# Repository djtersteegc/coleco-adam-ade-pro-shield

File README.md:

# coleco-adam-ade-pro-shield

This custom Arduino Mega 2560 shield compatible with [AdamNet Drive Emulator](https://github.com/Kalidomra/AdamNet-Drive-Emulator) (ADE) software by Sean Myers. The design is built to be compatible with the "Pro" version of the software available precompiled and ready for flashing on his repo.  I was inspired by John Lundy's original ADE shield design, but wanted something with a slightly smaller footprint and different SD card module.  This was accomplished by putting the LCD on stand-offs and mounting the card (and some other components) underneath it.

All components can be sourced from the usual low cost China based vendors for a total build cost of around $20.  Please see the assembly page for more details.

[Hardware Component Choices and Assembly](https://djtersteegc.github.io/coleco-adam-ade-pro-shield/assembly.html)

An interactive BOM and parts placement diagram is also available.

[Interactive Bill of Materials (BOM)](https://djtersteegc.github.io/coleco-adam-ade-pro-shield/ibom.html)

STL's and the [DesignSpark Mechanical](https://www.rs-online.com/designspark/mechanical-software) source file for a 3D printable enclosure are in the **enclosure** directory. There is a difference in power and USB connectors locations between the offical 2560 boards and the Chinese copies you can buy with the CH340 serial chips.  Pick the body file that matches the type you are using. The lid is snap fit, but you can also add a single M3x10mm screw if you wish to secure it further. Make sure to print seven copies of the button file.

If you wish to power your board from the 5V ADAMnet line, simply install and close jumper JP1.  Be warned there is no protection on the board from back feeding voltage into the Adam if you also power the Arduino via USB or it's DC jack connector, so only close this jumper when not using another power source on the Arduino.

# Getting a Board

If I have extra PCB's, they will be listed on Tindie (soon...).

Otherwise you can download the Gerbers and use your favorite fab (JLCPCB, PCBWay, etc.) to make your own batch.  It's a standard two layer, 1oz copper board with dimensions of 99mm x 61mm so it squeaks under the 100mm x 100mm limit of the cheap Chinese fabs.

# Hardware Revisions

### Version 1.0

Tested and working.

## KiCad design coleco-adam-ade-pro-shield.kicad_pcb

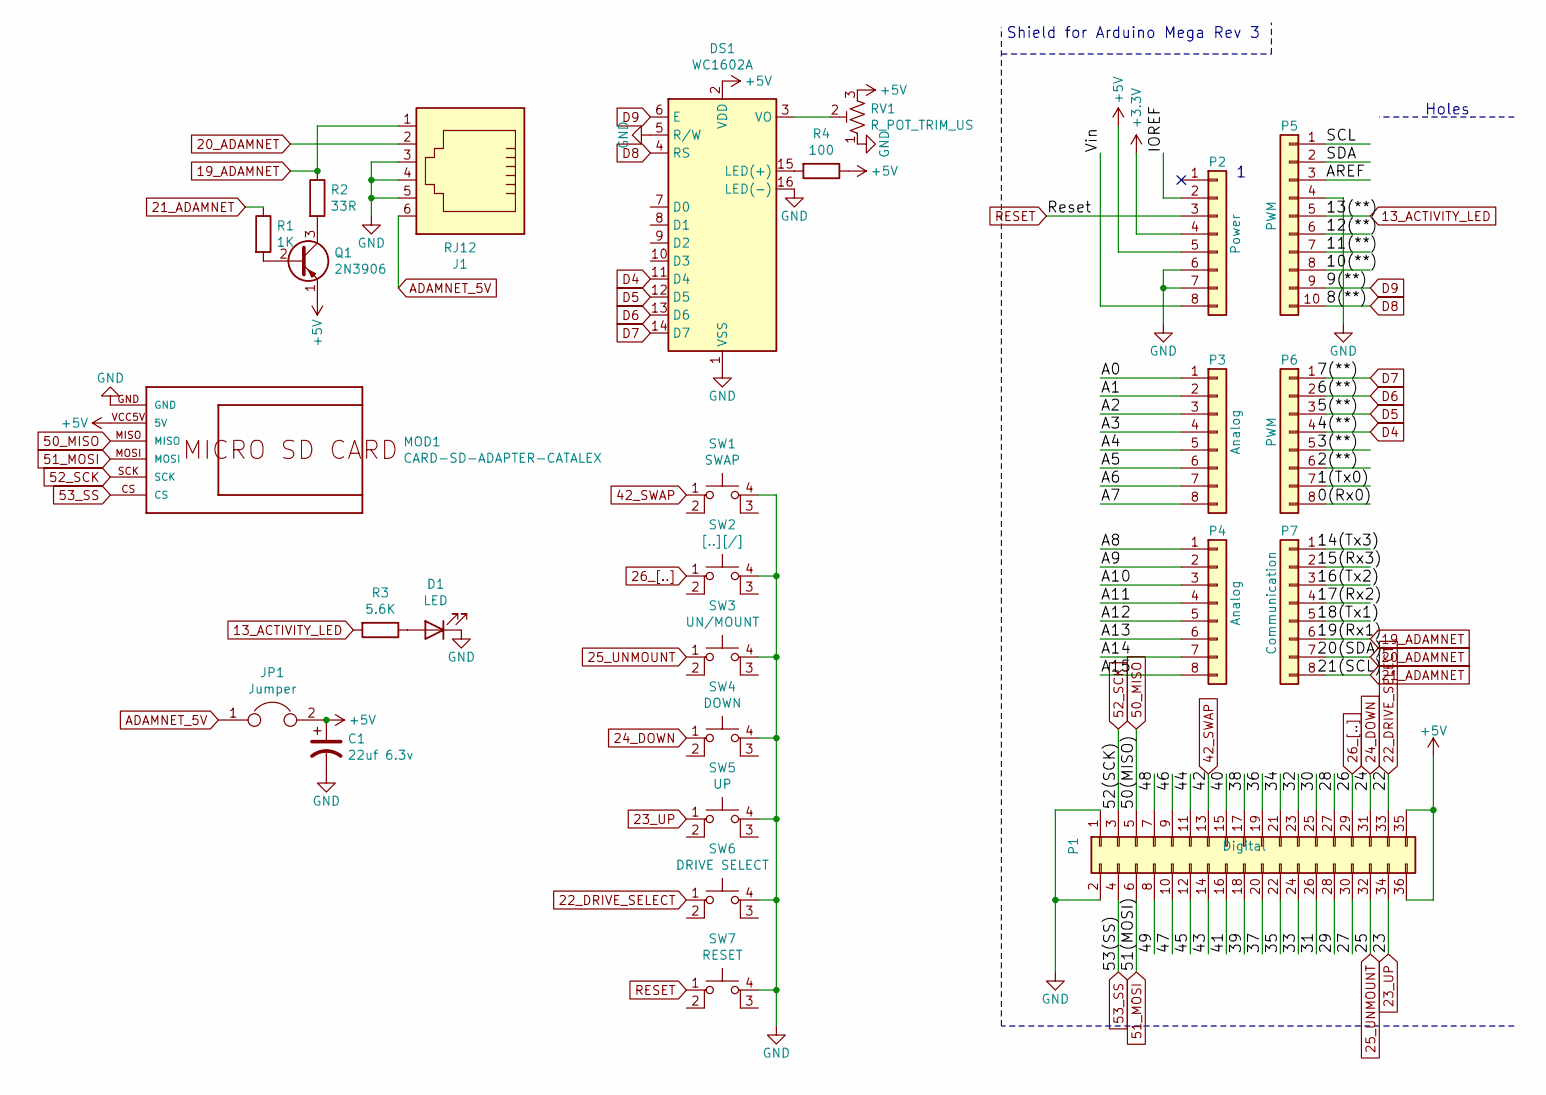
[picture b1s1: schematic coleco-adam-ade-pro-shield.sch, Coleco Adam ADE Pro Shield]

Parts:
C1: 22uf 6.3v; CP_Radial_D4.0mm_P1.50mm
D1: LED; LED_D5.0mm
DS1: WC1602A
J1: RJ12; RJ12_Amphenol_54601
JP1: Jumper; PinHeader_2x01_P2.54mm_Vertical
MOD1: CARD-SD-ADAPTER-CATALEX; Catalex-MicroSD-Card-Down
P1: Digital; Socket_Strip_Arduino_2x18
P2: Power; Socket_Strip_Arduino_1x08
P3, P4: Analog; Socket_Strip_Arduino_1x08
P5: PWM; Socket_Strip_Arduino_1x10
P6: PWM; Socket_Strip_Arduino_1x08
P7: Communication; Socket_Strip_Arduino_1x08
Q1: 2N3906; TO-92_Inline
R1: 1K; R_Axial_DIN0207_L6.3mm_D2.5mm_P7.62mm_Horizontal
R2: 33R; R_Axial_DIN0207_L6.3mm_D2.5mm_P7.62mm_Horizontal
R3: 5.6K; R_Axial_DIN0207_L6.3mm_D2.5mm_P7.62mm_Horizontal
R4: 100; R_Axial_DIN0207_L6.3mm_D2.5mm_P7.62mm_Horizontal
RV1: R_POT_TRIM_US; TRIM_3362P-1-103
SW1: SWAP; SW_TH_Tactile_Omron_B3F-10xx
SW2: [..][/]; SW_TH_Tactile_Omron_B3F-10xx
SW3: UN/MOUNT; SW_TH_Tactile_Omron_B3F-10xx
SW4: DOWN; SW_TH_Tactile_Omron_B3F-10xx
SW5: UP; SW_TH_Tactile_Omron_B3F-10xx
SW6: DRIVE SELECT; SW_TH_Tactile_Omron_B3F-10xx
SW7: RESET; SW_TH_Tactile_Omron_B3F-10xx

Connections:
13_ACTIVITY_LED: P5.5, R3.2
19_ADAMNET: J1.1, P7.6, R2.1
20_ADAMNET: J1.2, P7.7
21_ADAMNET: P7.8, R1.1
22_DRIVE_SELECT: P1.33, SW6.1
23_UP: P1.34, SW5.1
24_DOWN: P1.31, SW4.1
25_UNMOUNT: P1.32, SW3.1
26_[..]: P1.29, SW2.1
42_SWAP: P1.13, SW1.1
50_MISO: MOD1.MISO, P1.5
51_MOSI: MOD1.MOSI, P1.6
52_SCK: MOD1.SCK, P1.3
53_SS: MOD1.CS, P1.4
+3V3: P2.4
+5V: C1.1, DS1.2 (VDD), JP1.2, MOD1.VCC5V (5V), P1.35, P1.36, P2.5, Q1.1 (E), R4.1, RV1.3
/10(**): P5.8
/11(**): P5.7
/12(**): P5.6
/27: P1.30
/28: P1.27
/29: P1.28
/30: P1.25
/31: P1.26
/32: P1.23
/33: P1.24
/34: P1.21
/35: P1.22
/36: P1.19
/37: P1.20
/38: P1.17
/39: P1.18
/40: P1.15
/41: P1.16
/43: P1.14
/44: P1.11
/45: P1.12
/46: P1.9
/47: P1.10
/48: P1.7
/49: P1.8
/A0: P3.1
/A1: P3.2
/A2: P3.3
/A3: P3.4
/A4: P3.5
/A5: P3.6
/A6: P3.7
/A7: P3.8
/A8: P4.1
/A9: P4.2
/A10: P4.3
/A11: P4.4
/A12: P4.5
/A13: P4.6
/A14: P4.7
/A15: P4.8
/AREF: P5.3
/IOREF: P2.2
/SCL: P5.1
/SDA: P5.2
/Vin: P2.8
ADAMNET_5V: J1.6, JP1.1
D4: DS1.11 (D4), P6.4
D5: DS1.12 (D5), P6.3
D6: DS1.13 (D6), P6.2
D7: DS1.14 (D7), P6.1
D8: DS1.4 (RS), P5.10
D9: DS1.6 (E), P5.9
GND: C1.2, D1.1 (K), DS1.1 (VSS), DS1.5 (R/W), DS1.16 (LED(-)), J1.3, J1.4, J1.5, MOD1.GND, P1.1, P1.2, P2.6, P2.7, P5.4, RV1.1, SW1.4 (A), SW2.4 (A), SW3.4 (A), SW4.4 (A), SW5.4 (A), SW6.4 (A), SW7.4 (A)
unnamed: D1.2 (A), R3.1
unnamed: DS1.3 (VO), RV1.2
unnamed: DS1.15 (LED(+)), R4.2
unnamed: Q1.2 (B), R1.2
unnamed: Q1.3 (C), R2.2
RESET: P2.3, SW7.1

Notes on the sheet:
Shield for Arduino Mega Rev 3
Holes

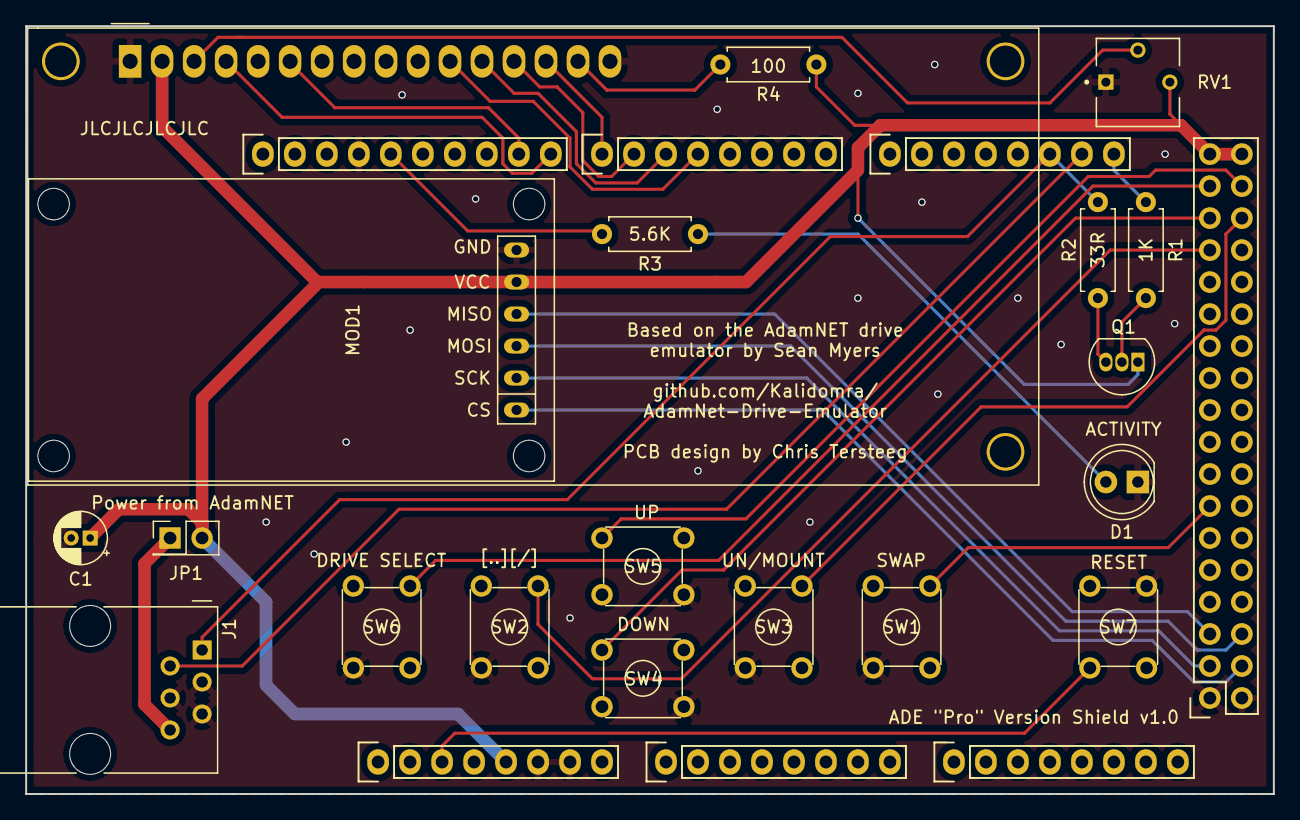
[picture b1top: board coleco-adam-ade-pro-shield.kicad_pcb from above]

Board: 2 copper layers, 99.1 x 61.0 mm, 26 parts (0 on the bottom side), 29 nets.

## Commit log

2021-02-28 Initial version sent to JCL
2021-03-06 Add some docs
2021-03-06 Update README.md
    Fix images
2021-03-06 Fix images
2021-03-06 Docs update
2021-03-06 doc updates
2022-10-29 Fixup 3D models
2022-10-29 Add enclosure
